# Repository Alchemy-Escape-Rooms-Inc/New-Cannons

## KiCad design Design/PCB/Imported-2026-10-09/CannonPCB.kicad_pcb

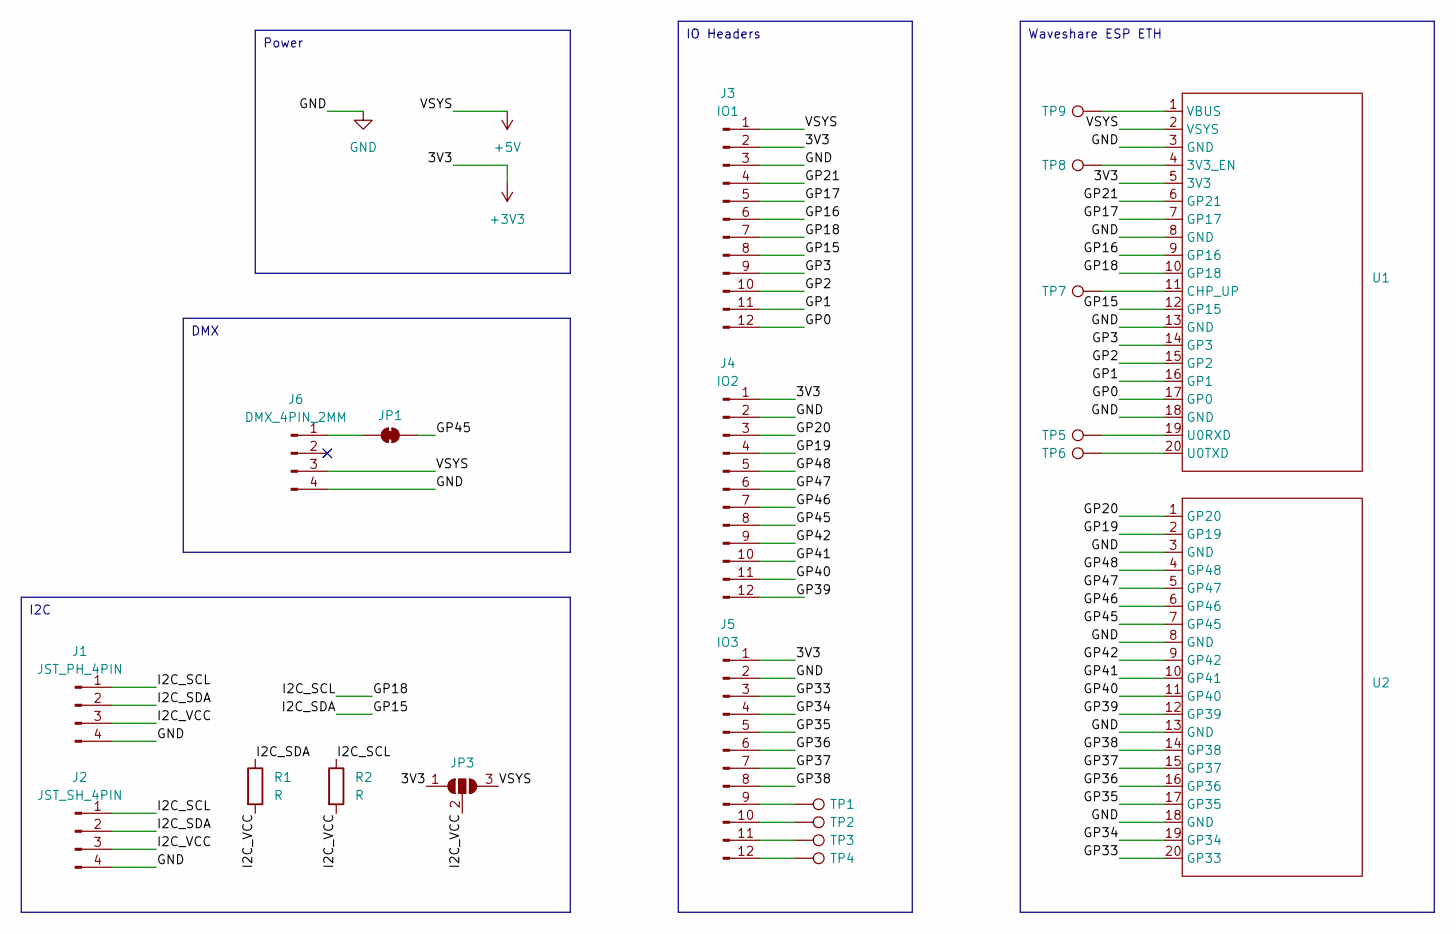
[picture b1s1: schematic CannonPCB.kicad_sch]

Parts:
J1: JST_PH_4PIN; JST_PH_B4B-PH-K_1x04_P2.00mm_Vertical
J2: JST_SH_4PIN; JST_SH_BM04B-SRSS-TB_1x04-1MP_P1.00mm_Vertical
J3: IO1; PinHeader_1x12_P2.54mm_Vertical
J4: IO2; PinHeader_1x12_P2.54mm_Vertical
J5: IO3; PinHeader_1x12_P2.54mm_Vertical
J6: DMX_4PIN_2MM; PinHeader_1x04_P2.00mm_Vertical
JP1: SolderJumper_2_Bridged; SolderJumper-2_P1.3mm_Bridged_RoundedPad1.0x1.5mm
JP3: SolderJumper_3_Open; SolderJumper-3_P1.3mm_Open_RoundedPad1.0x1.5mm
R1, R2: R; R_Axial_DIN0207_L6.3mm_D2.5mm_P10.16mm_Horizontal
TP1, TP2, TP3, TP4, TP5, TP6, TP7, TP8, TP9: TestPoint; TestPoint_THTPad_D2.0mm_Drill1.0mm
U1, U2: PinSocket_1x20_P2.54mm_Vertical

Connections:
+3V3: J3.2, J4.1, J5.1, JP3.1 (A), U1.5 (3V3)
+5V: J3.1, J6.3, JP3.3 (B), U1.2 (VSYS)
/GP0: J3.12, U1.17 (GP0)
/GP1: J3.11, U1.16 (GP1)
/GP2: J3.10, U1.15 (GP2)
/GP3: J3.9, U1.14 (GP3)
/GP15: J1.2, J2.2, J3.8, R1.1, U1.12 (GP15)
/GP16: J3.6, U1.9 (GP16)
/GP17: J3.5, U1.7 (GP17)
/GP18: J1.1, J2.1, J3.7, R2.1, U1.10 (GP18)
/GP19: J4.4, U2.2 (GP19)
/GP20: J4.3, U2.1 (GP20)
/GP21: J3.4, U1.6 (GP21)
/GP33: J5.3, U2.20 (GP33)
/GP34: J5.4, U2.19 (GP34)
/GP35: J5.5, U2.17 (GP35)
/GP36: J5.6, U2.16 (GP36)
/GP37: J5.7, U2.15 (GP37)
/GP38: J5.8, U2.14 (GP38)
/GP39: J4.12, U2.12 (GP39)
/GP40: J4.11, U2.11 (GP40)
/GP41: J4.10, U2.10 (GP41)
/GP42: J4.9, U2.9 (GP42)
/GP45: J4.8, JP1.2 (B), U2.7 (GP45)
/GP46: J4.7, U2.6 (GP46)
/GP47: J4.6, U2.5 (GP47)
/GP48: J4.5, U2.4 (GP48)
/I2C_VCC: J1.3, J2.3, JP3.2 (C), R1.2, R2.2
GND: J1.4, J2.4, J3.3, J4.2, J5.2, J6.4, U1.3 (GND), U1.8 (GND), U1.13 (GND), U1.18 (GND), U2.3 (GND), U2.8 (GND), U2.13 (GND), U2.18 (GND)
unnamed: J5.9, TP1.1
unnamed: J5.10, TP2.1
unnamed: J5.11, TP3.1
unnamed: J5.12, TP4.1
unnamed: J6.1, JP1.1 (A)
unnamed: TP8.1, U1.4 (3V3_EN)
unnamed: TP7.1, U1.11 (CHP_UP)
unnamed: TP5.1, U1.19 (U0RXD)
unnamed: TP6.1, U1.20 (U0TXD)
unnamed: TP9.1, U1.1 (VBUS)

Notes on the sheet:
Waveshare ESP ETH
I2C
DMX
IO Headers
Power

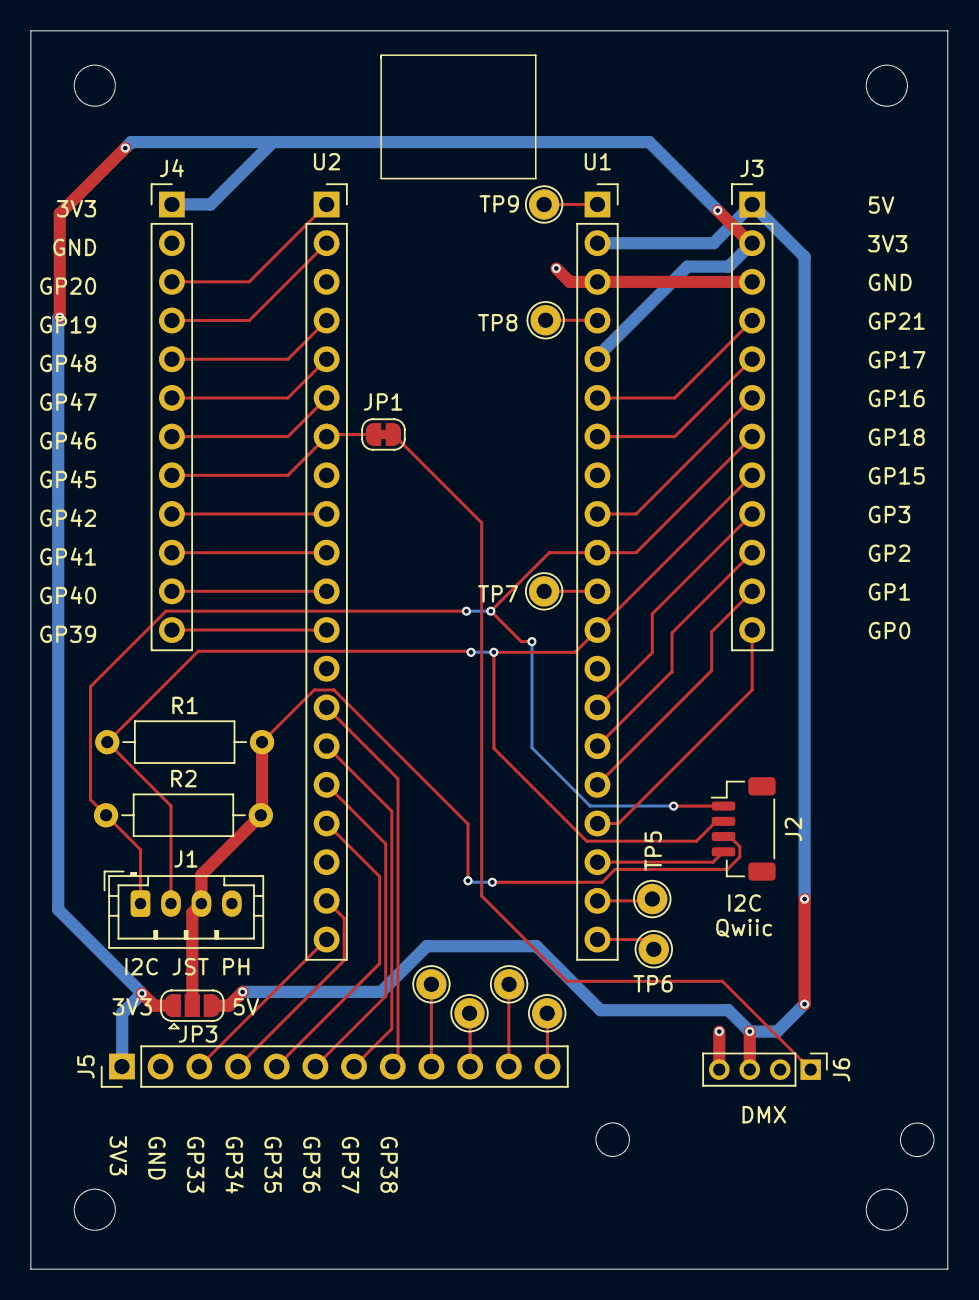
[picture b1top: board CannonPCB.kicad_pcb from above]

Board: 2 copper layers, 60.2 x 81.3 mm, 21 parts (0 on the bottom side), 39 nets.

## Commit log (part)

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2025-09-27 Update main.cpp
    Main improvements:
    Dynamic address detection - The I2C scanner now saves the ALS31300 address when found
    Smart initialization - Uses the detected address instead of hardcoded 0x65
    Fallback support - Still tries the original address if scan doesn't find ALS31300
    Updated diagnostics - Shows which address is actually being used
    Reset command support - MQTT reset now uses the correct detected address
2025-10-07 feat: Add configurable cannon ID and major improvements
    ✨ New Features:
    - Configurable cannon ID (change one constant in main.cpp)
    - Dynamic MQTT topic generation based on cannon ID
    - Auto-reconnection logic for MQTT
    - Watchdog timer for automatic restart on hang
    - Auto-status report after reset
2025-11-12 fix: Reset loaded/fired flags after cannon fires to enable continuous firing
    After firing, the loaded and fired flags were not being reset, preventing
    the cannon from detecting new load/fire cycles without physically removing
    and reloading the target.
    Changes:
    - Add resetLoadedAndFired() method to CannonStateView to reset state flags
    - Call reset method immediately after "Fired" event is published
2025-11-12 Fix snprintf syntax error and update COM port
    - Move snprintf initialization from global scope to setup() function
    - Change COM port from COM3 to COM4
2025-11-12 fix: Fix loaded detection logic and add angle/distance logging
    Fixed critical bug where cannon was always detecting as "loaded" when
    the distance sensor was valid, regardless of actual distance reading.
    Changes:
    - Fix loaded detection: Now uses threshold-based detection (≤50mm)
    instead of always returning true when sensor is valid
    - Change threshold from 120mm to 50mm (background reads 76-78mm)
2025-11-12 chore: Update upload port from COM3 to COM4
2025-11-12 Fix snprintf syntax error
2025-11-12 Add angle change logging similar to distance logging
2025-11-12 Add auto-upload script for pulling latest code and uploading to ESP32
2025-11-13 Add comprehensive AI Trading Bot with ML and self-learning
    Implemented a multifaceted AI-powered automated trading bot with:
    Core Features:
    - Machine learning models (XGBoost, LightGBM, RF, LSTM)
    - Ensemble predictions with confidence scoring
    - Self-learning from prediction results and trades
    - 50+ engineered features and technical indicators
2025-11-13 Fix critical bugs found in code audit
    - Added store_backtest_result() method to Database class
    - Replaced invalid db.execute() calls with store_backtest_result()
    - Implemented _evaluate_todays_predictions() method
    - All 3 critical issues from audit now resolved
    Code is now 100% production-ready with all bugs fixed.
2025-11-13 Add final verification checklist with mathematical proofs
2025-11-13 Remove AI trading bot - moved to separate repository
    The AI trading bot has been moved to its own dedicated repository.
    New-Cannons should only contain escape room related files.
2025-11-13 Remove angle jump rejection that was blocking legitimate angle updates
    The angle jump rejection logic (MAX_ANGLE_JUMP_DEG threshold) was preventing
    the filtered angle from converging to the raw angle when the difference exceeded
    10 degrees. This caused the system to get stuck rejecting valid angle readings.
    Now the filter uses pure exponential moving average without rejection, allowing
    it to smoothly converge to the correct angle even after large changes while still
    providing noise smoothing.
2025-11-13 Remove all angle filtering - use raw angle values for MQTT
    Removed angle filtering at both levels:
    1. ALS31300 sensor: Removed Cartesian-space filtering in getAngle()
    2. main.cpp: Removed exponential moving average filtering
    Now publishes raw angle values directly to MQTT without any filtering
    or jump rejection. X/Y magnetometer readings still have basic noise
    filtering, but angle calculation is direct.
2025-11-14 Final cannon firmware with MQTT telemetry and raw angle tracking
    Key features:
    - Raw angle values without filtering for accurate cannon positioning
    - MQTT telemetry for angle, loaded, and fired events
    - Distance filtering with configurable alpha
    - Watchdog timer for system stability
    - I2C bus scanning and recovery
2025-11-14 Add AI Trading Bot archive for download
2025-11-17 Add complete ESP32 pop lock system with web interface
    Implemented a comprehensive electronic pop lock control system:
    - Web-based code entry interface optimized for iPad/tablets
    - Support for multiple solenoid locks (6 by default, easily expandable)
    - Configurable access codes mapped to specific lockboxes
    - Auto-timeout for lock activation (2 seconds default)
    - MQTT integration for remote monitoring and control
2025-11-17 Add escape room industry news scraper with email notifications
    Features:
    - Monitors 10+ escape room industry news sources and blogs
    - Sends email notifications with new articles
    - Interactive feedback system in emails
    - Smart deduplication to avoid sending duplicate articles
    - Easy configuration via .env file
2025-11-17 Add Fort Lauderdale real estate search and analysis tool
    This comprehensive tool searches multiple sources for Fort Lauderdale properties,
    analyzes them for investment potential and personal residence suitability, and
    sends daily email reports with findings.
    Features:
    - Multi-source property search (MLS, auctions, public records)
    - Real Broward County foreclosure auction integration
2026-01-14 Remove non-cannon files and restore repository to cannon firmware only
    Removed unrelated files that were mistakenly added:
    - Fort Lauderdale house search tool (Python)
    - Various documentation and scripts not related to cannon firmware
    The cannon firmware with watchdog protocol remains in src/main.cpp
2026-01-28 fix: Use legacy MQTT topic format without slash for cannon events
    Remove the slash between cannon ID and topic suffix (Hor, Loaded, Fired)
    to match the legacy format expected by the game. This fixes the conflict
    where 'triggered' and 'clear' messages were being sent to different topics.
    Topics now use: MermaidsTale/Cannon{id}Loaded, MermaidsTale/Cannon{id}Fired,
    MermaidsTale/Cannon{id}Hor (without slash before suffix)
    https://claude.ai/code/session_018QU2ZVHPPu6gEg3GtgFyvP
2026-02-14 Add MANIFEST.h and bridge MqttConfig.h/main.cpp to manifest system
    Adds the self-documenting firmware manifest (MANIFEST.h) as the single
    source of truth for all device constants, pin assignments, network config,
    and operational documentation with @TAG markers for the Grimoire parser.
    MqttConfig.h now bridges to manifest:: values via cfg:: namespace.
    main.cpp config namespace and VERSION define now reference manifest::.
    Zero changes to function calls or logic.
